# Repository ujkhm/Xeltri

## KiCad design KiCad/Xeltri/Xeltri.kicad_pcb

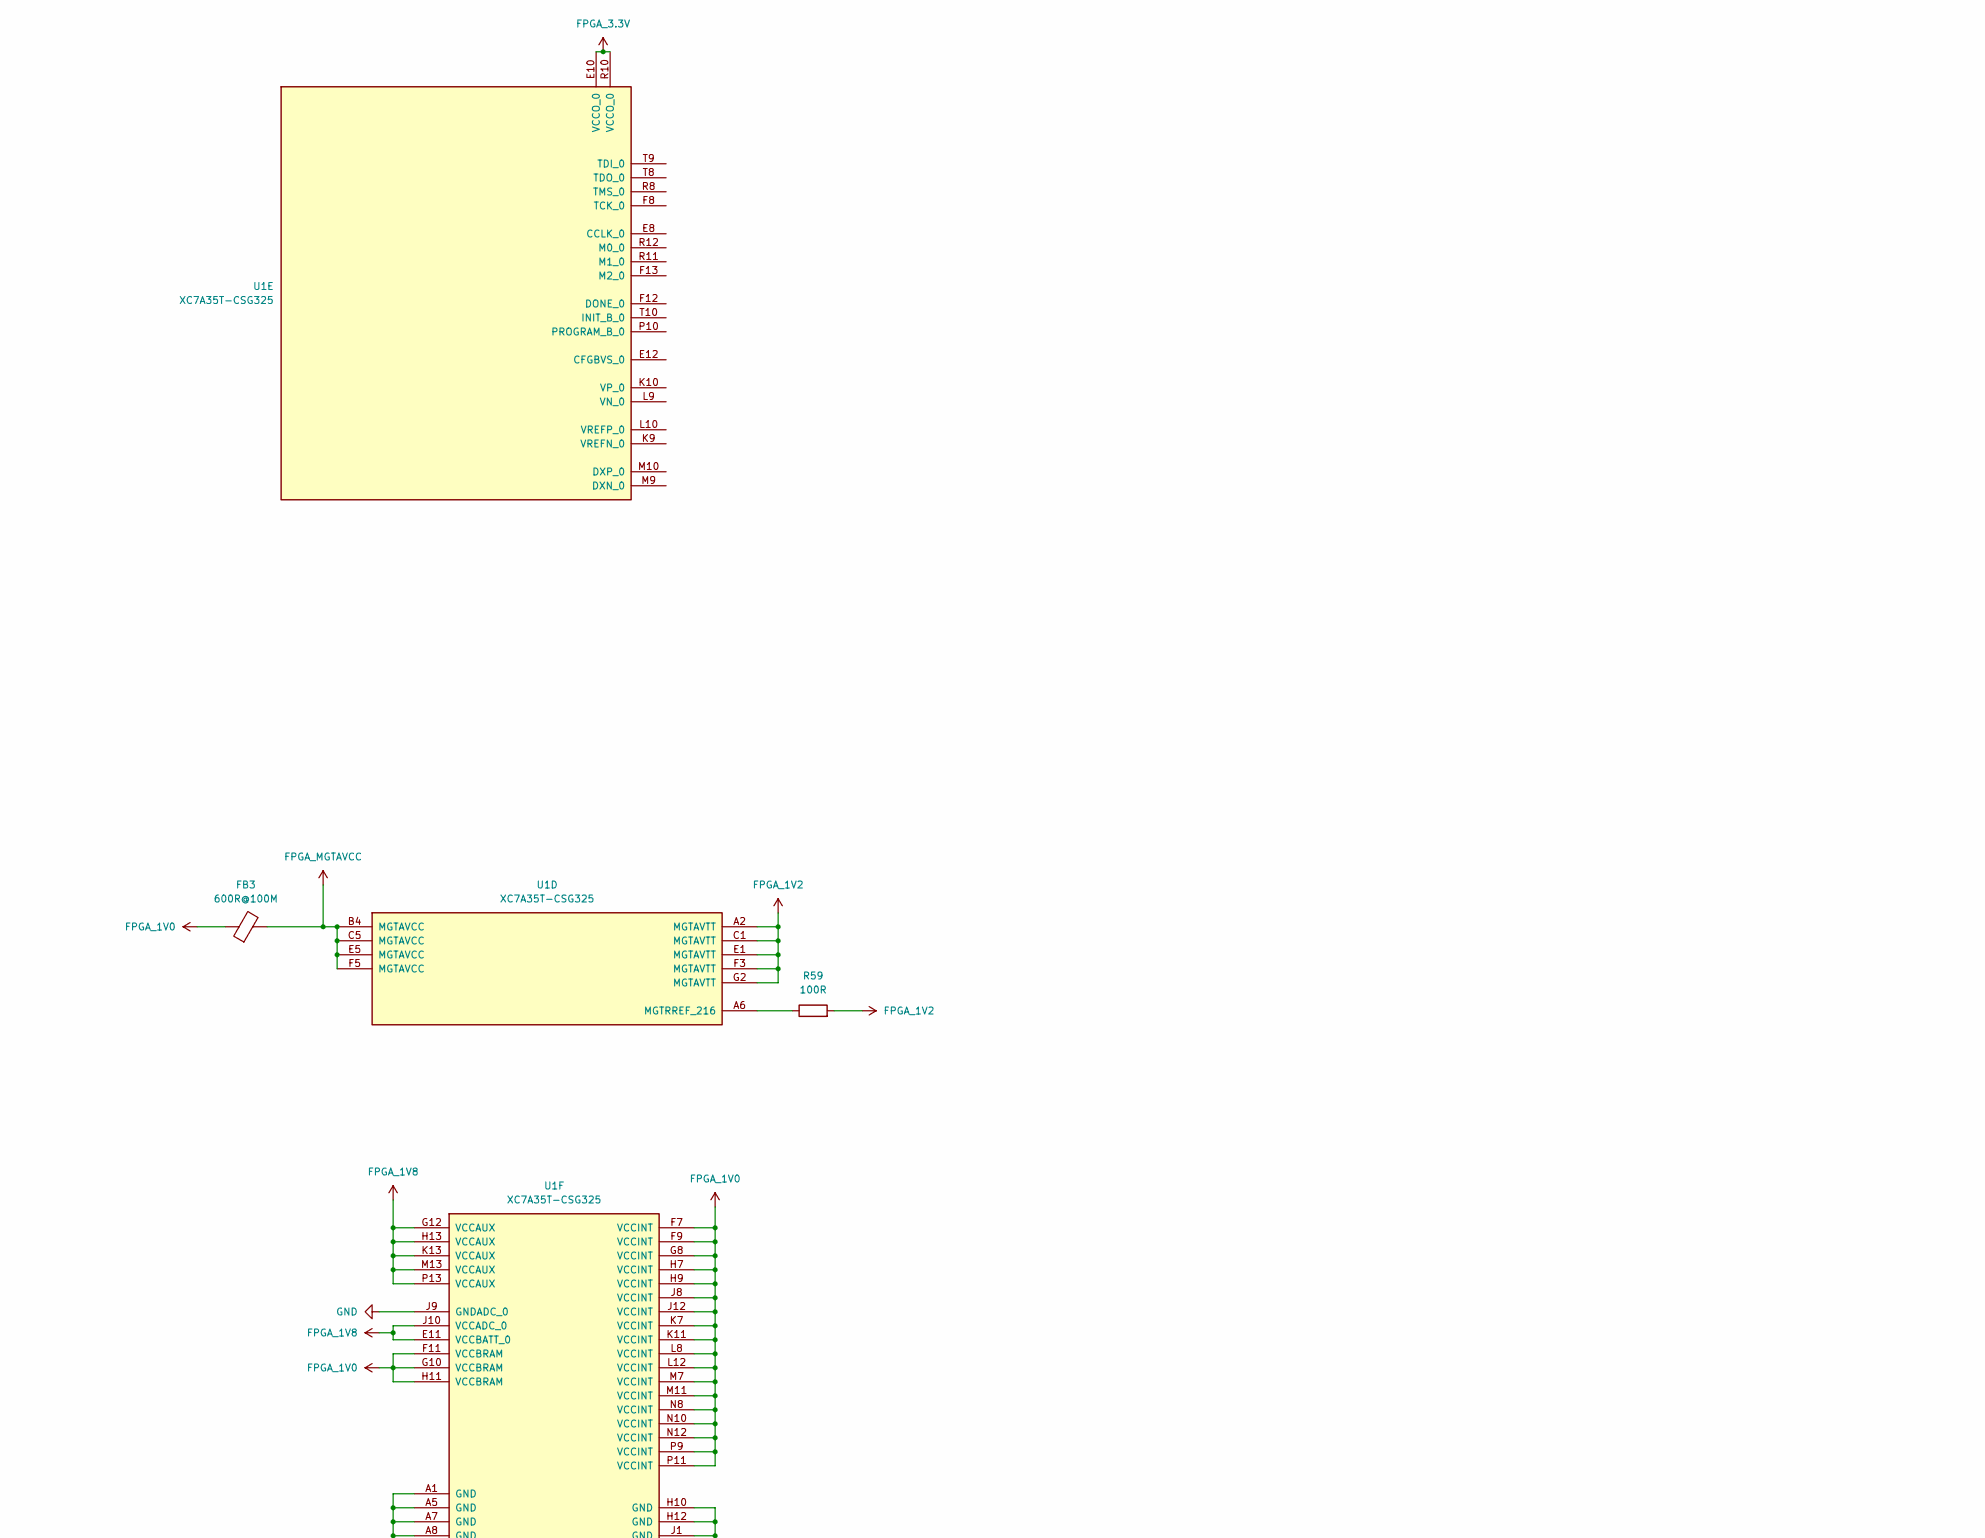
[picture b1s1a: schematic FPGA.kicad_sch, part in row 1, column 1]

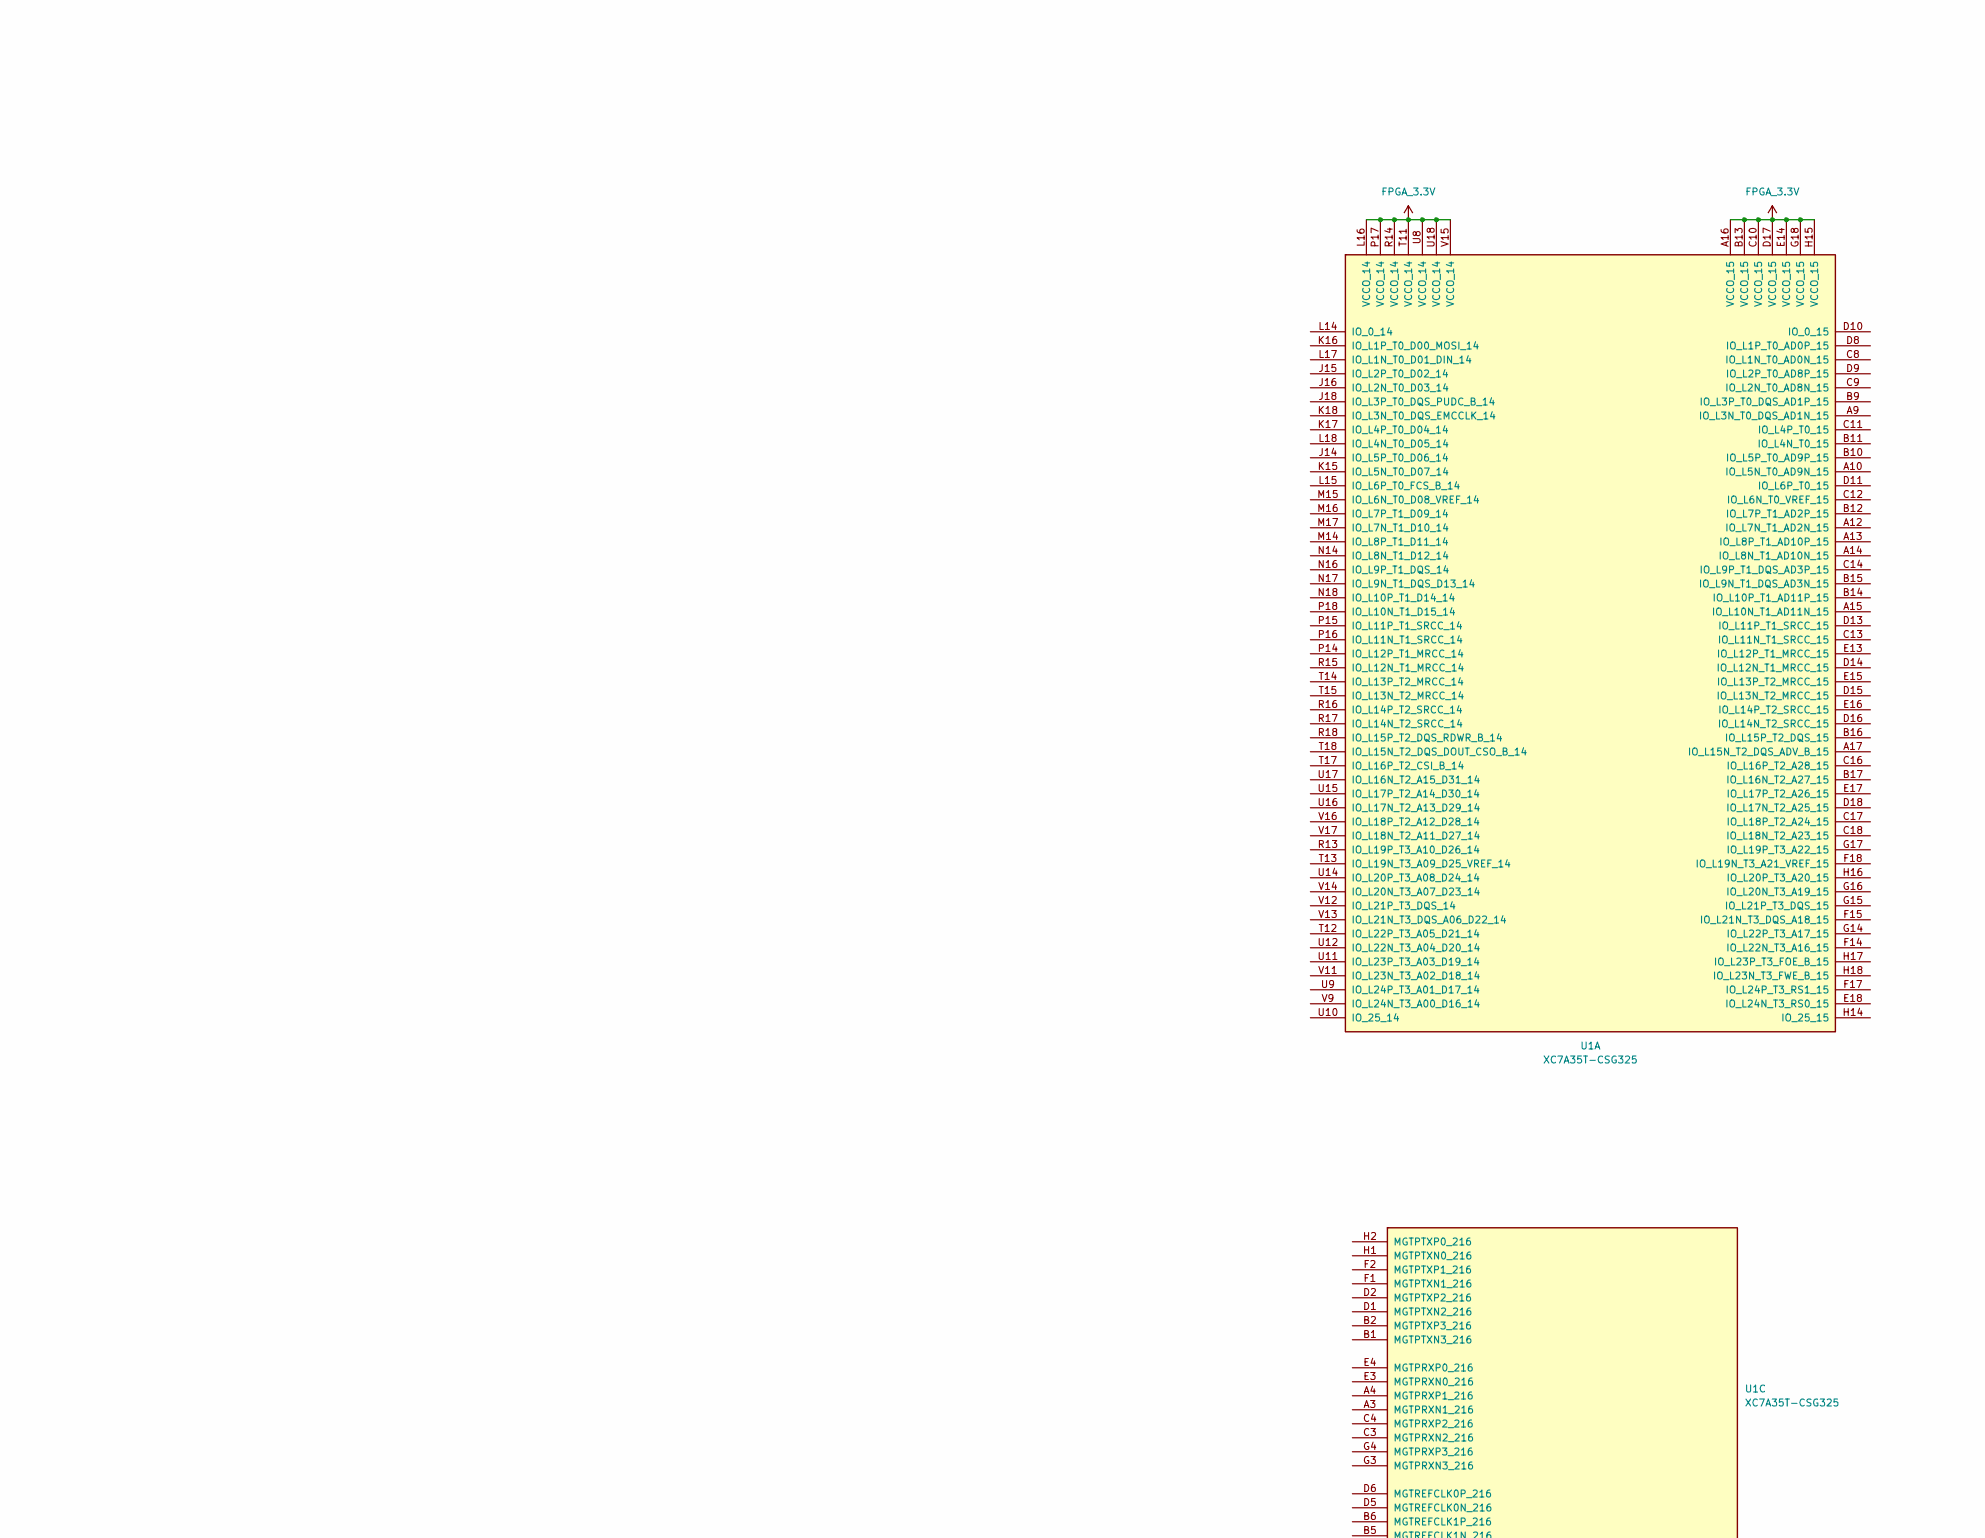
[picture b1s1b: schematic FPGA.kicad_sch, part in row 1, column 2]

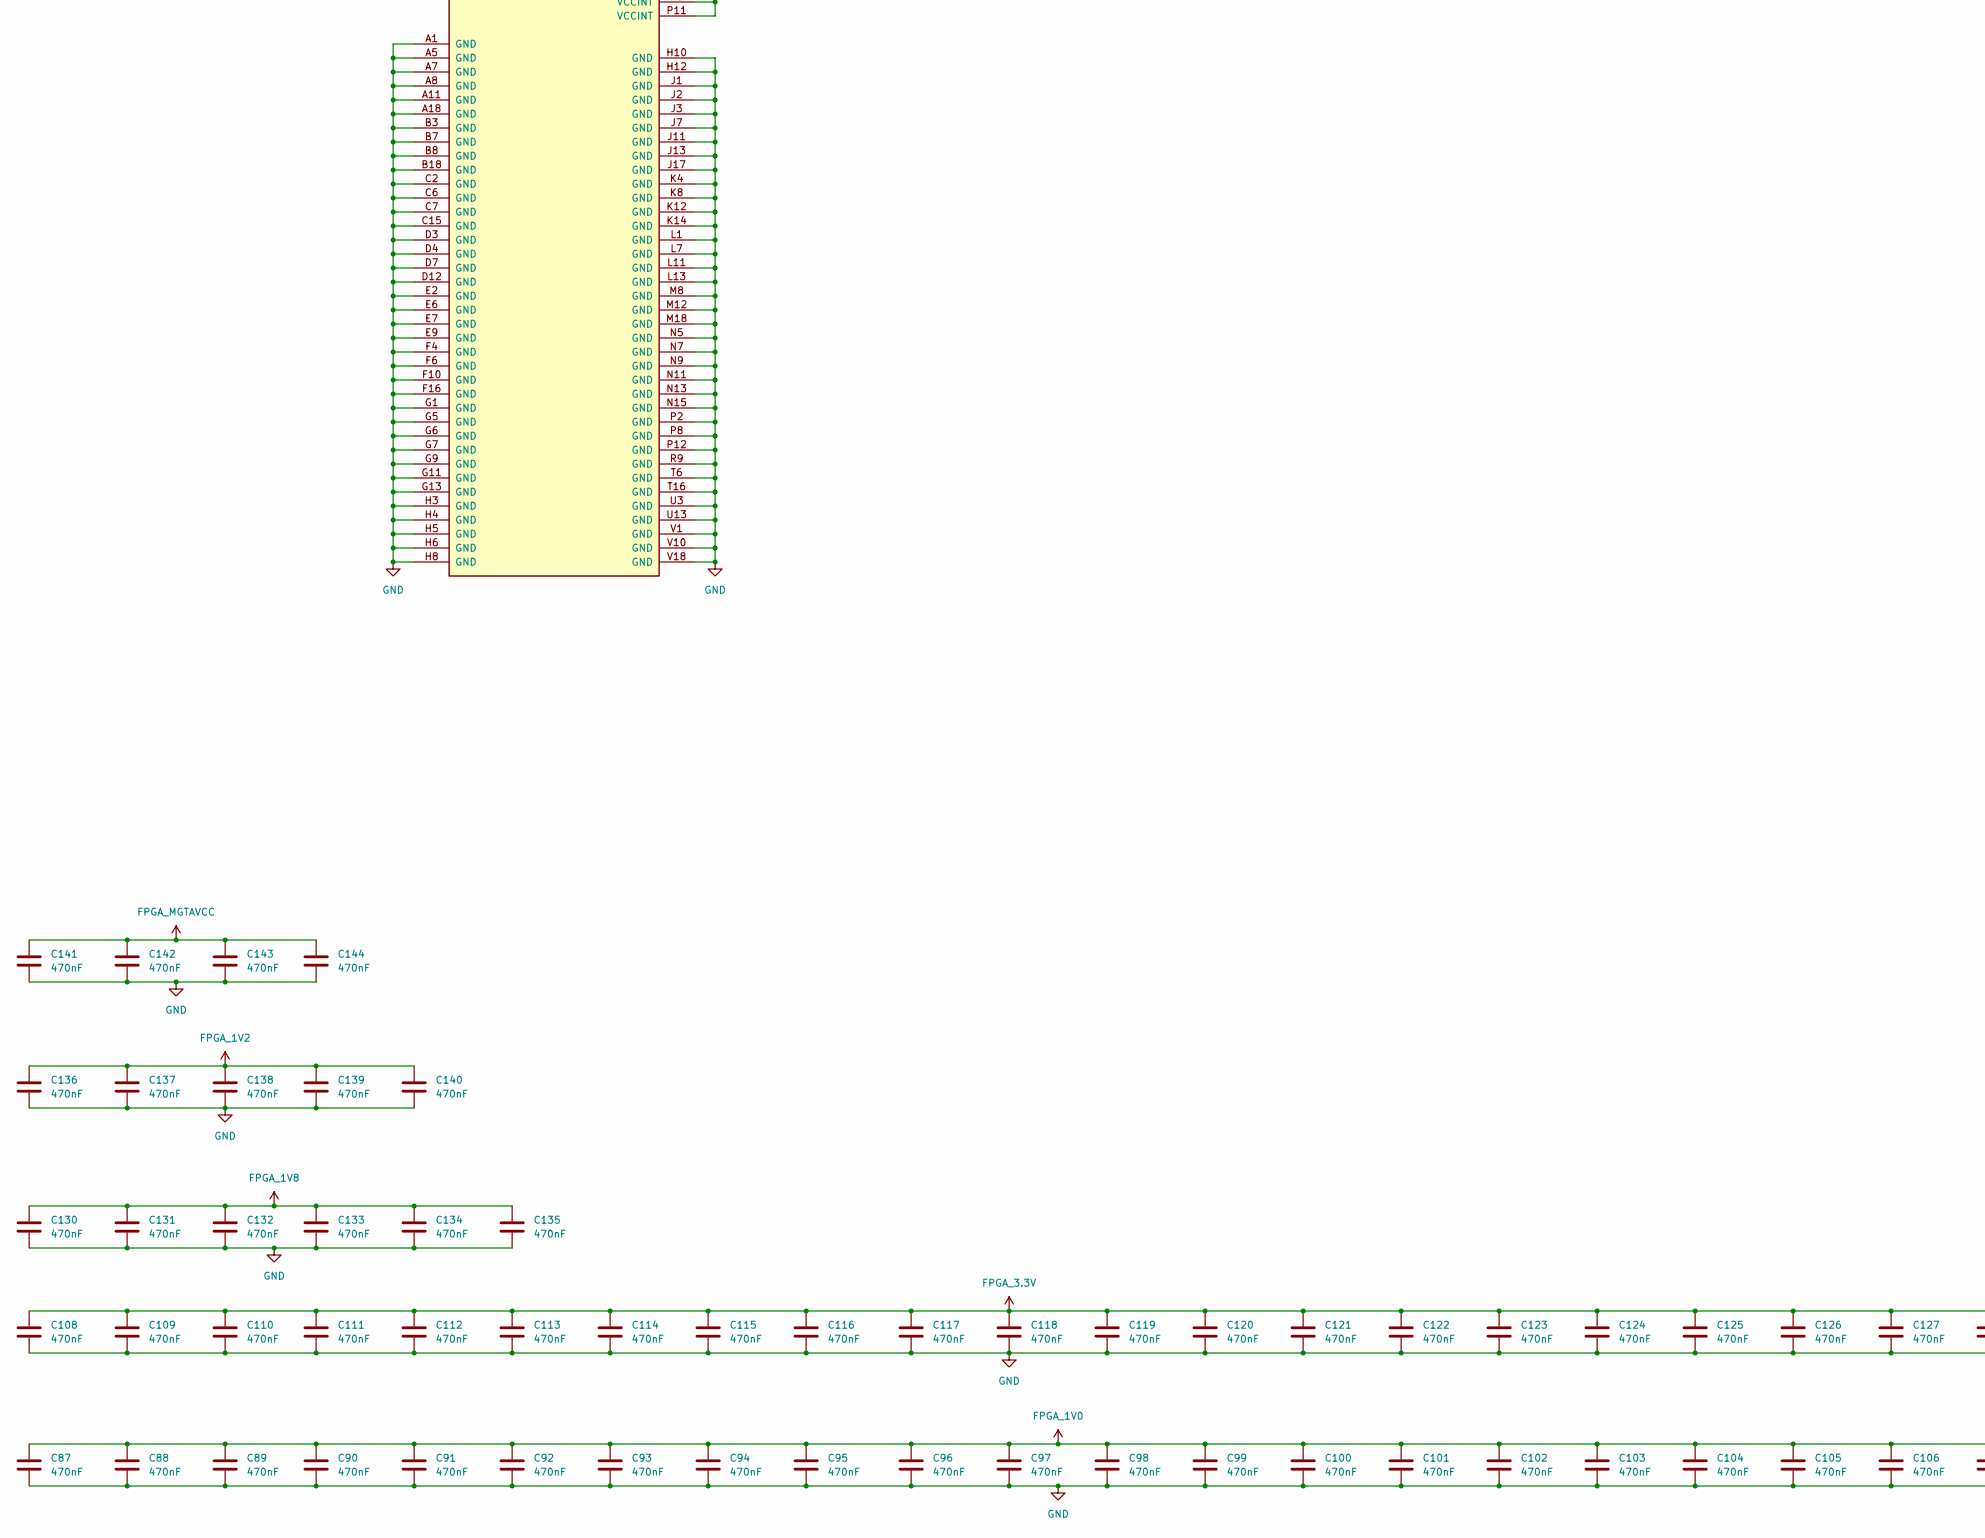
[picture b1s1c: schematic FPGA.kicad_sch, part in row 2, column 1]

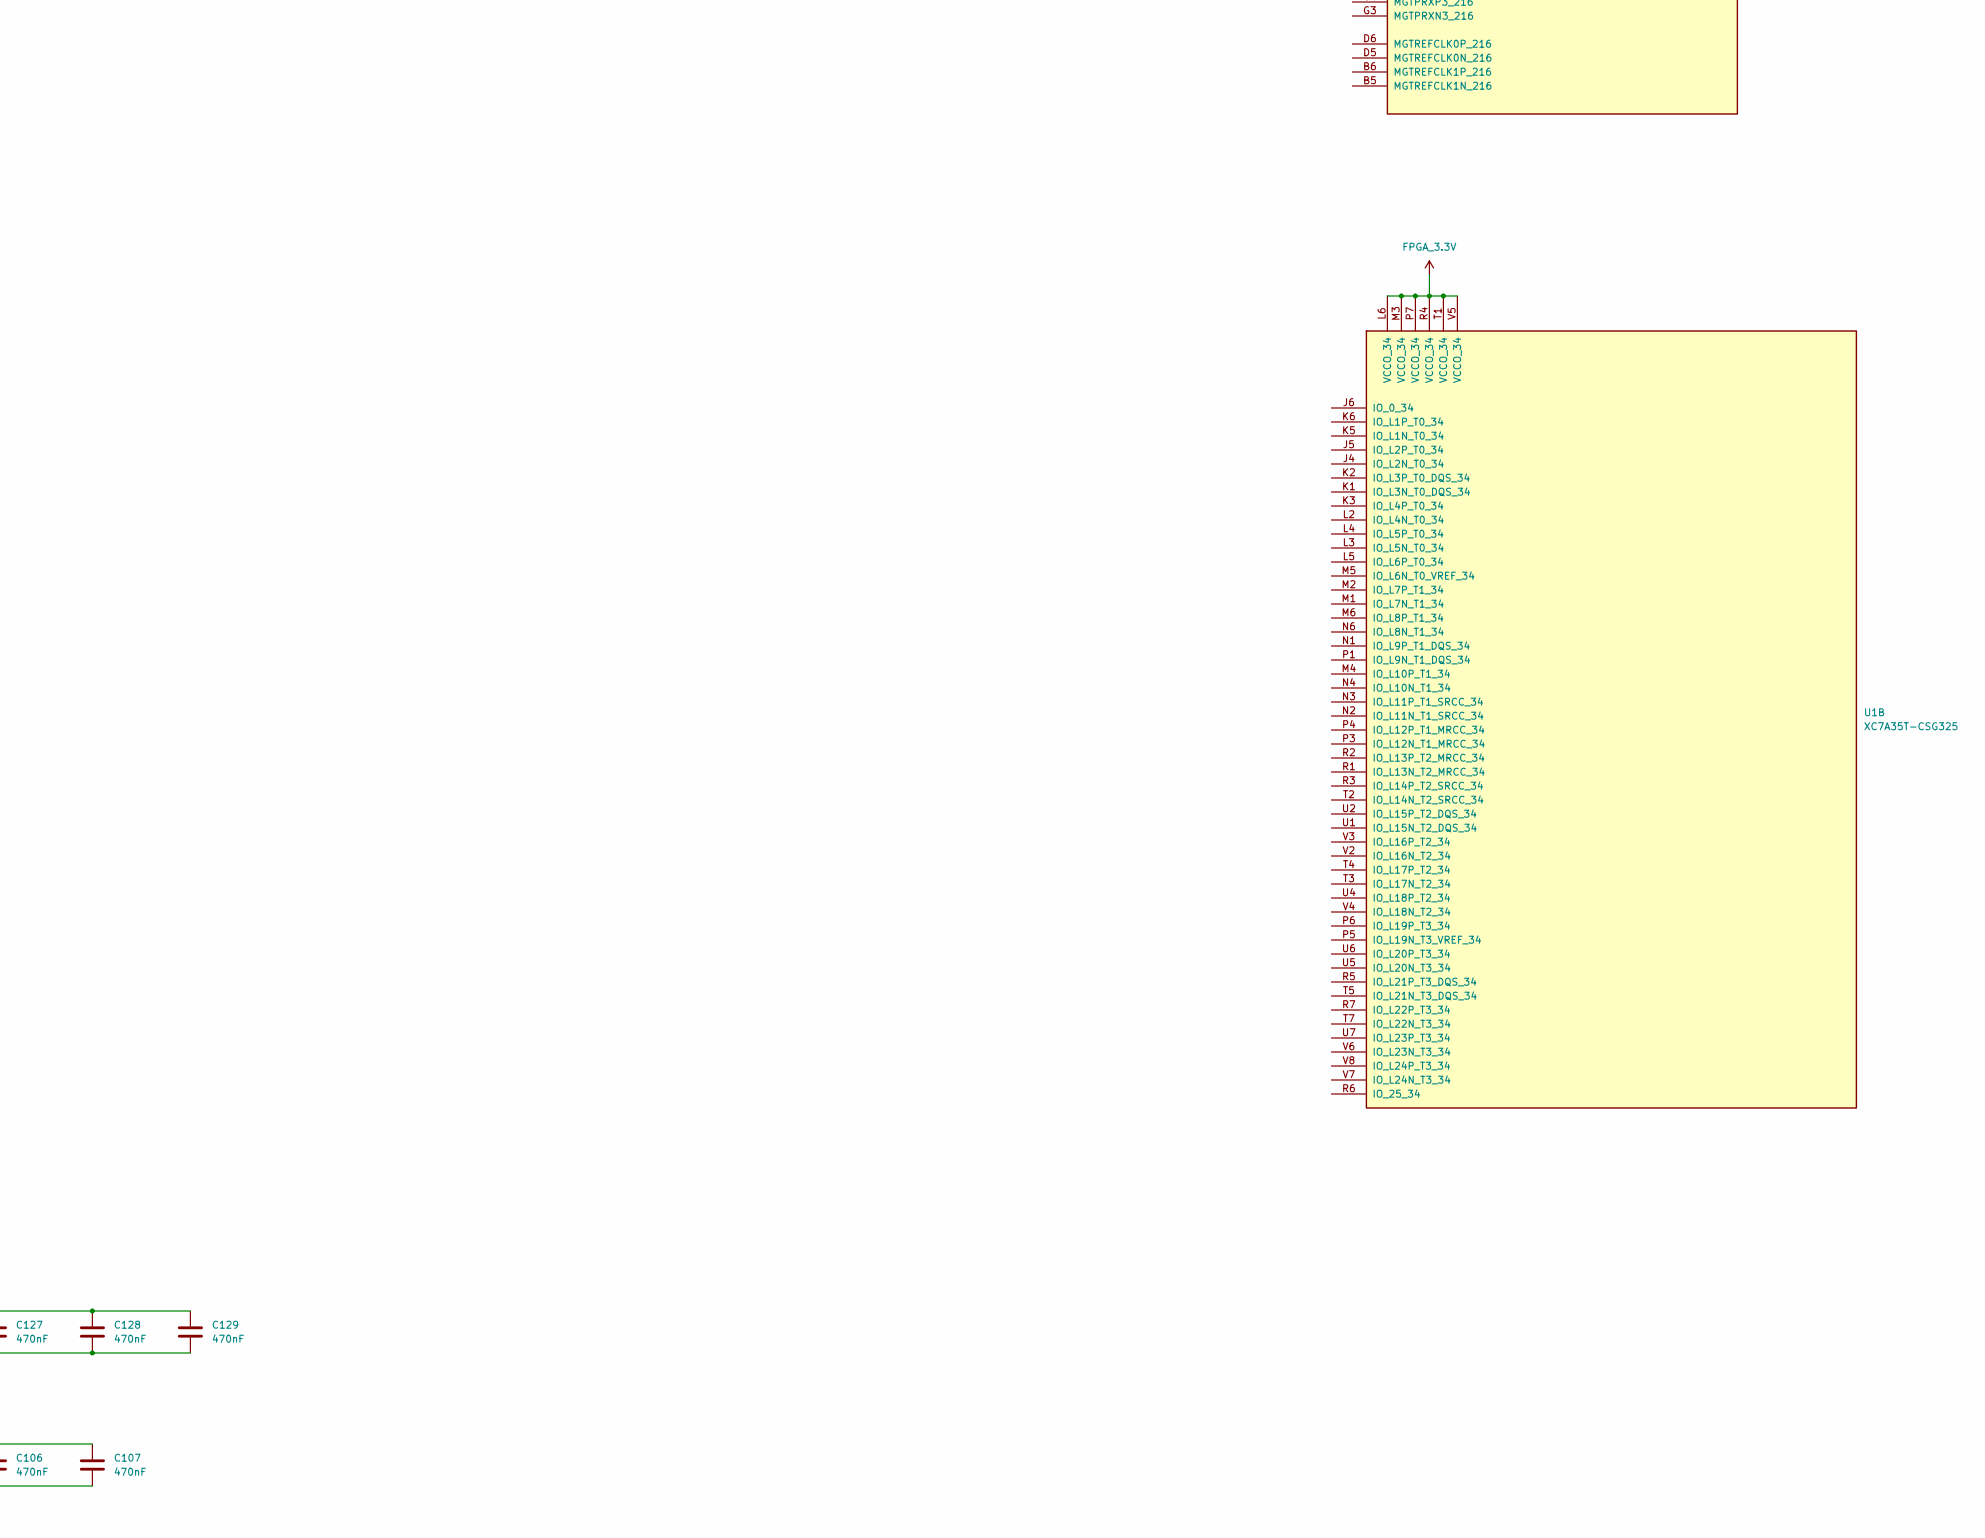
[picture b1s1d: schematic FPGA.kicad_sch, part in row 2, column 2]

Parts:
C87, C88, C89, C90, C91, C92, C93, C94, C95, C96, C97, C98, C99, C100, C101, C102, C103, C104, C105, C106, C107, C108, C109, C110, C111, C112, C113, C114, C115, C116, C117, C118, C119, C120, C121, C122, C123, C124, C125, C126, C127, C128, C129, C130, C131, C132, C133, C134, C135, C136, C137, C138, C139, C140, C141, C142, C143, C144: 470nF; C_0402_1005Metric
FB3: 600R@100M; L_0402_1005Metric
R59: 100R; R_0402_1005Metric
U1: XC7A35T-CSG325; Xilinx_CSG325

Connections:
FPGA_1V0: C87.1, C88.1, C89.1, C90.1, C91.1, C92.1, C93.1, C94.1, C95.1, C96.1, C97.1, C98.1, C99.1, C100.1, C101.1, C102.1, C103.1, C104.1, C105.1, C106.1, C107.1, FB3.1, U1.F7 (VCCINT), U1.F9 (VCCINT), U1.F11 (VCCBRAM), U1.G8 (VCCINT), U1.G10 (VCCBRAM), U1.H7 (VCCINT), U1.H9 (VCCINT), U1.H11 (VCCBRAM), U1.J8 (VCCINT), U1.J12 (VCCINT), U1.K7 (VCCINT), U1.K11 (VCCINT), U1.L8 (VCCINT), U1.L12 (VCCINT), U1.M7 (VCCINT), U1.M11 (VCCINT), U1.N8 (VCCINT), U1.N10 (VCCINT), U1.N12 (VCCINT), U1.P9 (VCCINT), U1.P11 (VCCINT)
FPGA_1V2: C136.1, C137.1, C138.1, C139.1, C140.1, R59.2, U1.A2 (MGTAVTT), U1.C1 (MGTAVTT), U1.E1 (MGTAVTT), U1.F3 (MGTAVTT), U1.G2 (MGTAVTT)
FPGA_1V8: C130.1, C131.1, C132.1, C133.1, C134.1, C135.1, U1.E11 (VCCBATT_0), U1.G12 (VCCAUX), U1.H13 (VCCAUX), U1.J10 (VCCADC_0), U1.K13 (VCCAUX), U1.M13 (VCCAUX), U1.P13 (VCCAUX)
FPGA_3.3V: C108.1, C109.1, C110.1, C111.1, C112.1, C113.1, C114.1, C115.1, C116.1, C117.1, C118.1, C119.1, C120.1, C121.1, C122.1, C123.1, C124.1, C125.1, C126.1, C127.1, C128.1, C129.1, U1.A16 (VCCO_15), U1.B13 (VCCO_15), U1.C10 (VCCO_15), U1.D17 (VCCO_15), U1.E10 (VCCO_0), U1.E14 (VCCO_15), U1.G18 (VCCO_15), U1.H15 (VCCO_15), U1.L6 (VCCO_34), U1.L16 (VCCO_14), U1.M3 (VCCO_34), U1.P7 (VCCO_34), U1.P17 (VCCO_14), U1.R4 (VCCO_34), U1.R10 (VCCO_0), U1.R14 (VCCO_14), U1.T1 (VCCO_34), U1.T11 (VCCO_14), U1.U8 (VCCO_14), U1.U18 (VCCO_14), U1.V5 (VCCO_34), U1.V15 (VCCO_14)
FPGA_MGTAVCC: C141.1, C142.1, C143.1, C144.1, FB3.2, U1.B4 (MGTAVCC), U1.C5 (MGTAVCC), U1.E5 (MGTAVCC), U1.F5 (MGTAVCC)
GND: C87.2, C88.2, C89.2, C90.2, C91.2, C92.2, C93.2, C94.2, C95.2, C96.2, C97.2, C98.2, C99.2, C100.2, C101.2, C102.2, C103.2, C104.2, C105.2, C106.2, C107.2, C108.2, C109.2, C110.2, C111.2, C112.2, C113.2, C114.2, C115.2, C116.2, C117.2, C118.2, C119.2, C120.2, C121.2, C122.2, C123.2, C124.2, C125.2, C126.2, C127.2, C128.2, C129.2, C130.2, C131.2, C132.2, C133.2, C134.2, C135.2, C136.2, C137.2, C138.2, C139.2, C140.2, C141.2, C142.2, C143.2, C144.2, U1.A1 (GND), U1.A5 (GND), U1.A7 (GND), U1.A8 (GND), U1.A11 (GND), U1.A18 (GND), U1.B3 (GND), U1.B7 (GND), U1.B8 (GND), U1.B18 (GND), U1.C2 (GND), U1.C6 (GND), U1.C7 (GND), U1.C15 (GND), U1.D3 (GND), U1.D4 (GND), U1.D7 (GND), U1.D12 (GND), U1.E2 (GND), U1.E6 (GND), U1.E7 (GND), U1.E9 (GND), U1.F4 (GND), U1.F6 (GND), U1.F10 (GND), U1.F16 (GND), U1.G1 (GND), U1.G5 (GND), U1.G6 (GND), U1.G7 (GND), U1.G9 (GND), U1.G11 (GND), U1.G13 (GND), U1.H3 (GND), U1.H4 (GND), U1.H5 (GND), U1.H6 (GND), U1.H8 (GND), U1.H10 (GND), U1.H12 (GND), U1.J1 (GND), U1.J2 (GND), U1.J3 (GND), U1.J7 (GND), U1.J9 (GNDADC_0), U1.J11 (GND), U1.J13 (GND), U1.J17 (GND), U1.K4 (GND), U1.K8 (GND), U1.K12 (GND), U1.K14 (GND), U1.L1 (GND), U1.L7 (GND), U1.L11 (GND), U1.L13 (GND), U1.M8 (GND), U1.M12 (GND), U1.M18 (GND), U1.N5 (GND), U1.N7 (GND), U1.N9 (GND), U1.N11 (GND), U1.N13 (GND), U1.N15 (GND), U1.P2 (GND), U1.P8 (GND), U1.P12 (GND), U1.R9 (GND), U1.T6 (GND), U1.T16 (GND), U1.U3 (GND), U1.U13 (GND), U1.V1 (GND), U1.V10 (GND), U1.V18 (GND); also elsewhere on the board
unnamed: R59.1, U1.A6 (MGTRREF_216)

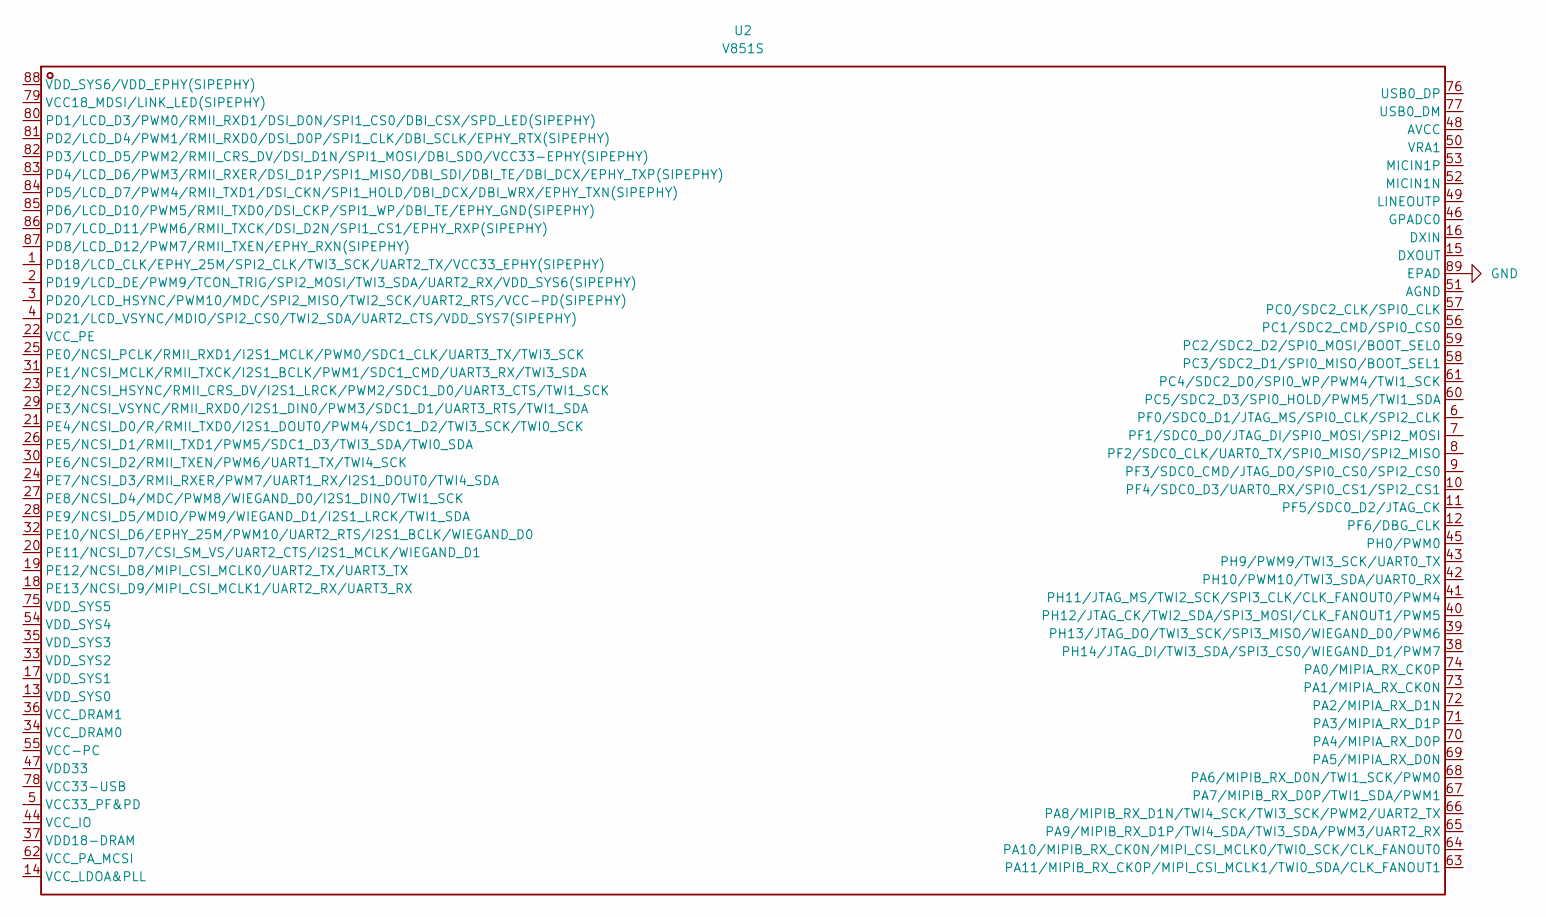
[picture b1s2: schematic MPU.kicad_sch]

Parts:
U2: V851S; QFN-88_L9.0-W9.0-P0.35-TL-EP6.5; LCSC Part C5365286

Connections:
GND: U2.89 (EPAD); also elsewhere on the board

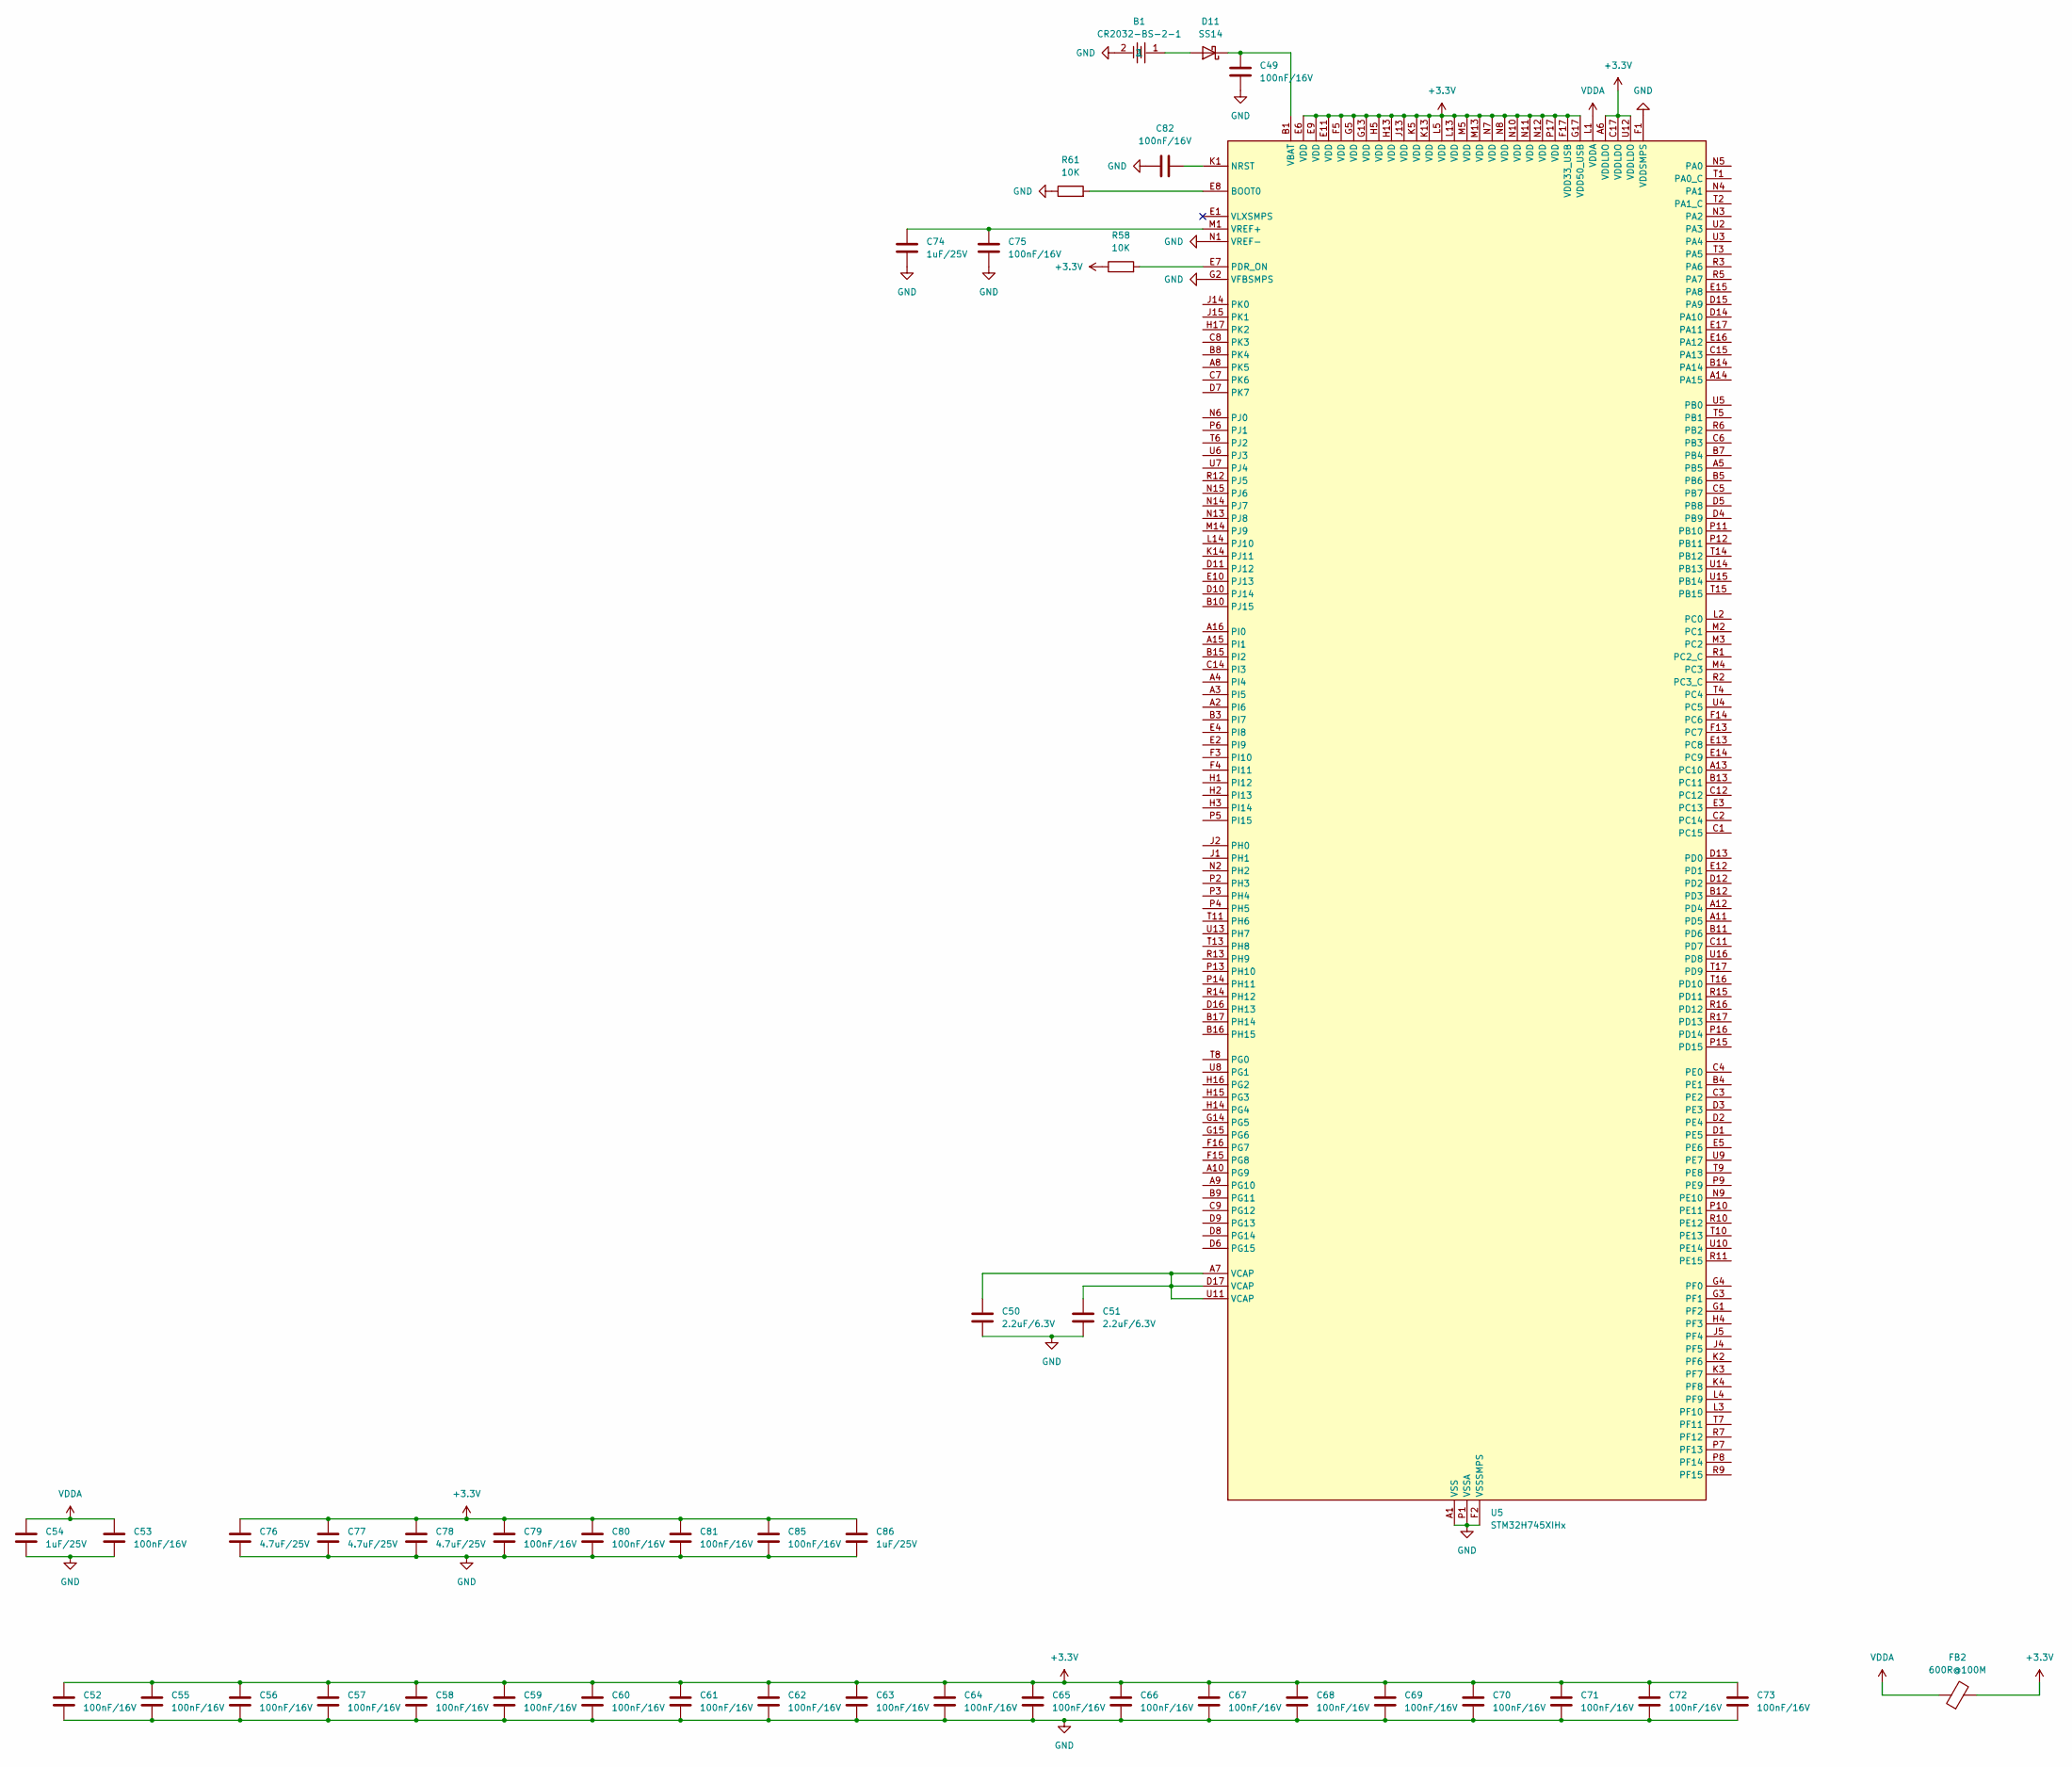
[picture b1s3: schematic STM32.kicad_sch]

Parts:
B1: CR2032-BS-2-1; BAT-TH_BS-2-1; LCSC Part C70376
C49, C52, C53, C55, C56, C57, C58, C59, C60, C61, C62, C63, C64, C65, C66, C67, C68, C69, C70, C71, C72, C73, C75, C79, C80, C81, C82, C85: 100nF/16V; C_0402_1005Metric; LCSC Part C1525
C50, C51: 2.2uF/6.3V; C_0402_1005Metric; LCSC Part C12530
C54, C74, C86: 1uF/25V; C_0402_1005Metric; LCSC Part C52923
C76, C77, C78: 4.7uF/25V; C_0805_2012Metric; LCSC Part C1779
D11: SS14; D_SMA
FB2: 600R@100M; L_0402_1005Metric
R58, R61: 10K; R_0402_1005Metric
U5: STM32H745XIHx; TFBGA-265_14x14mm_Layout17x17_P0.8mm

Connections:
+3.3V: C52.1, C55.1, C56.1, C57.1, C58.1, C59.1, C60.1, C61.1, C62.1, C63.1, C64.1, C65.1, C66.1, C67.1, C68.1, C69.1, C70.1, C71.1, C72.1, C73.1, C76.1, C77.1, C78.1, C79.1, C80.1, C81.1, C85.1, C86.1, FB2.2, R58.1, U5.A6 (VDDLDO), U5.C17 (VDDLDO), U5.E6 (VDD), U5.E9 (VDD), U5.E11 (VDD), U5.F5 (VDD), U5.F17 (VDD33_USB), U5.G5 (VDD), U5.G13 (VDD), U5.G17 (VDD50_USB), U5.H5 (VDD), U5.H13 (VDD), U5.J13 (VDD), U5.K5 (VDD), U5.K13 (VDD), U5.L5 (VDD), U5.L13 (VDD), U5.M5 (VDD), U5.M13 (VDD), U5.N7 (VDD), U5.N8 (VDD), U5.N10 (VDD), U5.N11 (VDD), U5.N12 (VDD), U5.P17 (VDD), U5.U12 (VDDLDO); also elsewhere on the board
GND: B1.2, C49.2, C50.1, C51.2, C52.2, C53.2, C54.2, C55.2, C56.2, C57.2, C58.2, C59.2, C60.2, C61.2, C62.2, C63.2, C64.2, C65.2, C66.2, C67.2, C68.2, C69.2, C70.2, C71.2, C72.2, C73.2, C74.2, C75.2, C76.2, C77.2, C78.2, C79.2, C80.2, C81.2, C82.1, C85.2, C86.2, R61.1, U5.A1 (VSS), U5.A17 (VSS), U5.B2 (VSS), U5.B6 (VSS), U5.C10 (VSS), U5.C13 (VSS), U5.C16 (VSS), U5.F1 (VDDSMPS), U5.F2 (VSSSMPS), U5.G2 (VFBSMPS), U5.G7 (VSS), U5.G8 (VSS), U5.G9 (VSS), U5.G10 (VSS), U5.G11 (VSS), U5.G16 (VSS), U5.H7 (VSS), U5.H8 (VSS), U5.H9 (VSS), U5.H10 (VSS), U5.H11 (VSS), U5.J3 (VSS), U5.J7 (VSS), U5.J8 (VSS), U5.J9 (VSS), U5.J10 (VSS), U5.J11 (VSS), U5.J16 (VSS), U5.J17 (VSS), U5.K7 (VSS), U5.K8 (VSS), U5.K9 (VSS), U5.K10 (VSS), U5.K11 (VSS), U5.K15 (VSS), U5.L7 (VSS), U5.L8 (VSS), U5.L9 (VSS), U5.L10 (VSS), U5.L11 (VSS), U5.L15 (VSS), U5.M15 (VSS), U5.N1 (VREF-), U5.N16 (VSS), U5.P1 (VSSA), U5.R4 (VSS), U5.R8 (VSS), U5.T12 (VSS), U5.U1 (VSS), U5.U17 (VSS); also elsewhere on the board
unnamed: C50.2, C51.1, U5.A7 (VCAP), U5.D17 (VCAP), U5.U11 (VCAP)
unnamed: B1.1, D11.2 (A)
unnamed: C49.1, D11.1 (K), U5.B1 (VBAT)
unnamed: R61.2, U5.E8 (BOOT0)
unnamed: C82.2, U5.K1 (NRST)
unnamed: R58.2, U5.E7 (PDR_ON)
unnamed: C74.1, C75.1, U5.M1 (VREF+)
VDDA: C53.1, C54.1, FB2.1, U5.L1 (VDDA)
